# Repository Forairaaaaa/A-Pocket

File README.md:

# A-Pocket - 基于全志A133的掌上终端

视频介绍：[【开源】 自 制 手 机 ：【一】PDA？_哔哩哔哩_bilibili](https://www.bilibili.com/video/BV11t4y1W7DJ#reply114174036736)

虽然是奔着DIY手机去的，不知咋的就做成PDA了（

由于屏幕特殊，性价比极低，不建议复刻除核心板外的其他东西。

### 硬件组成

- **核心板**：板载全志A133邮票孔模块、USB-OTG、USB-Debug、带MIC的3.5mm耳机接口、扬声器接口、电池接口、MPU6050、RTC等，单板即可满足正常工作。另外由板对板引出显示屏接口和USB接口供拓展。未引出A133提供的摄像头接口。
- **拓展板**：板载LCD背光电路、USB5V的DC-DC升压电路和USB-HUB电路等。
- **散热**：背壳贴石墨烯，由导热硅垫传热

### 软件组成

核心模组厂商提供了安卓10和Ubuntu的镜像，要适配屏幕只需要简单修改设备树的配置文件即可。

### 物件参考链接

- [HelperBoard A133核心板（安卓10、ub，全志A133，内置5G-WIFI）-淘宝网 (taobao.com)](https://item.taobao.com/item.htm?spm=a1z09.2.0.0.fae32e8dKwhqRd&id=646476965103&_u=o2bdtj0f16a5)
- [适用智力快车儿童视频学习机早教机锂电池3.7V大容量10000mah充电-tmall.com天猫](https://detail.tmall.com/item.htm?id=613087896696&spm=a1z09.2.0.0.fae32e8dKwhqRd&_u=o2bdtj0fb0d2)   955565
- [3.8寸IPS液晶显示模块 电容触摸屏1024*600 JD9168, LVDS接口-tmall.com天猫](https://detail.tmall.com/item.htm?id=652122490131&spm=a1z09.2.0.0.fae32e8dKwhqRd&_u=o2bdtj0f7da0)

### 缺点

屏幕性价比低，屏占比低，核心模组也比较贵

板对板连接导致厚度大，扬声器音质很烂

### 待改进

改用量产的手机MIPI屏幕，但需要学写驱动（泪目

主控想改用RK3399或RK3588，但价格~~

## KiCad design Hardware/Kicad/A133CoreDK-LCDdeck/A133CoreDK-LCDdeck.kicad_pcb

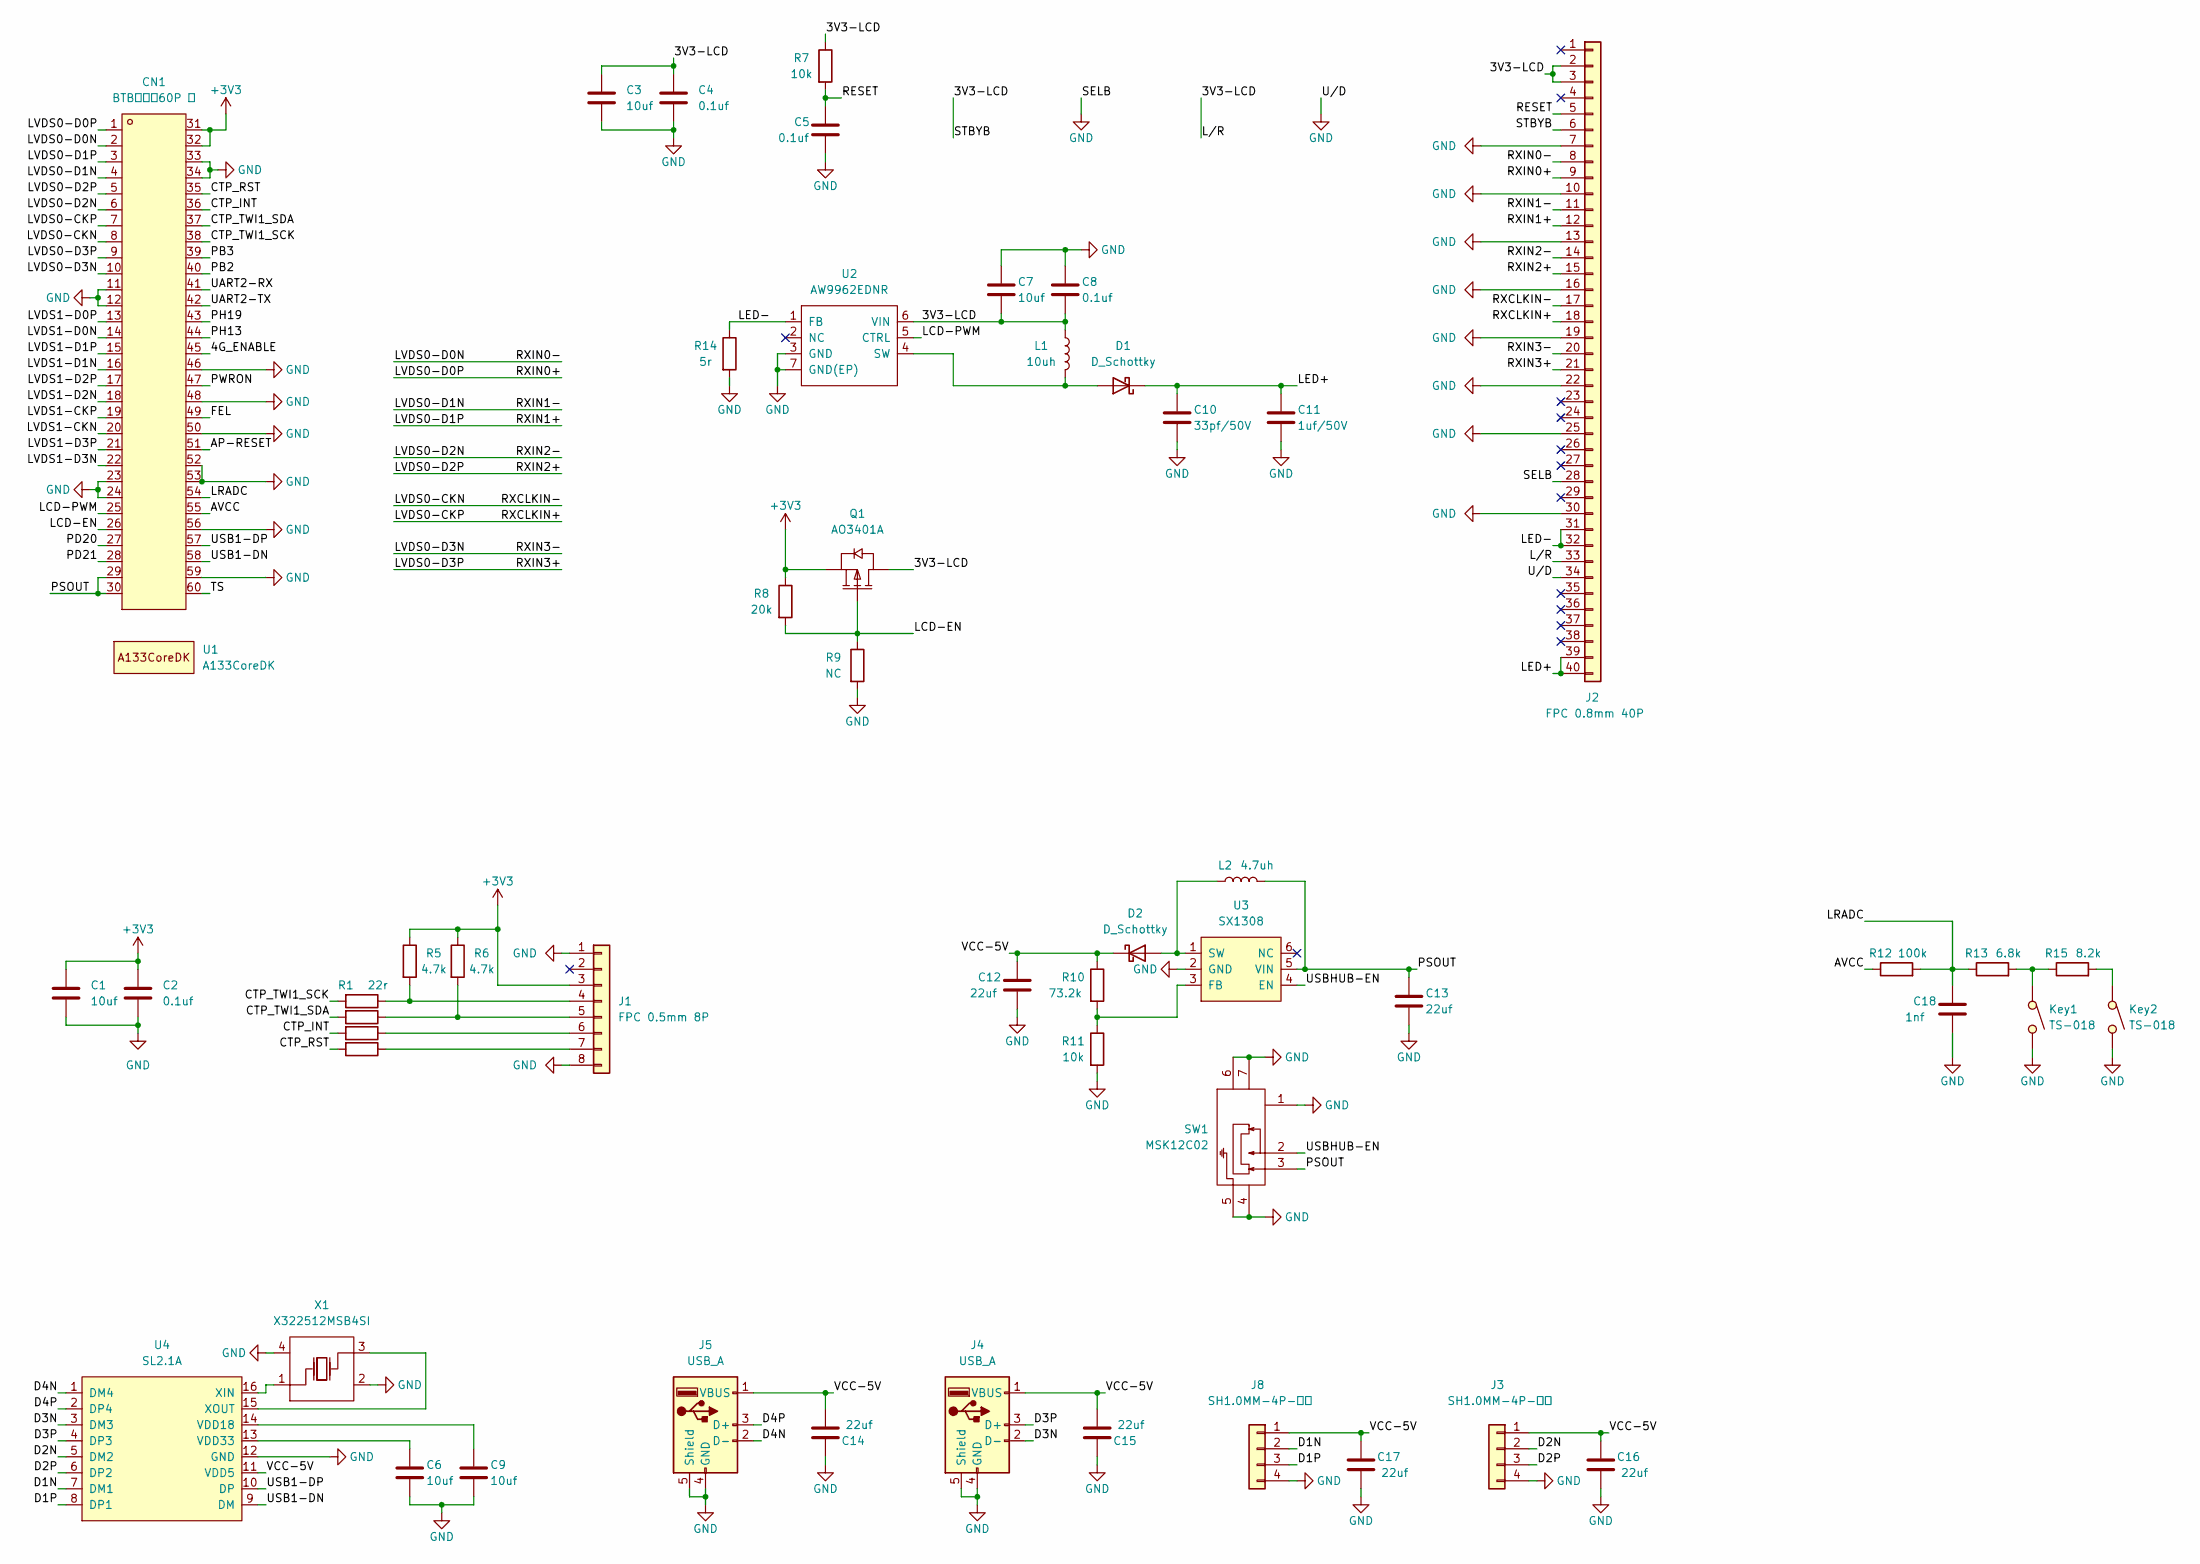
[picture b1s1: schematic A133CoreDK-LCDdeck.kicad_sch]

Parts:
C1, C3, C6, C7, C9: 10uf; C_0402_1005Metric
C2, C4, C5, C8: 0.1uf; C_0402_1005Metric
C10: 33pf/50V; C_0603_1608Metric
C11: 1uf/50V; C_0603_1608Metric
C12, C13, C14, C15, C16, C17: 22uf; C_0603_1608Metric
C18: 1nf; C_0402_1005Metric
CN1: BTB板对板60P 母
D1, D2: D_Schottky; D_SOD-123
J1: FPC 0.5mm 8P; TE_0-1734839-8_1x08-1MP_P0.5mm_Horizontal
J2: FPC 0.8mm 40P; TE_4-1734839-0_1x40-1MP_P0.5mm_Horizontal
J3, J8: SH1.0MM-4P-卧贴; SH1.0MM-卧贴-4P-CONN-SMD_1.0T-4P
J4, J5: USB_A; USB-A-SMD_FUS270-FSBW5K
Key1, Key2: TS-018; SW-SMD_TS24CA
L1: 10uh; CD32贴片电感-IND-SMD_L3.5-W3.0
L2: 4.7uh; CD32贴片电感-IND-SMD_L3.5-W3.0
Q1: AO3401A; SOT-23
R1, R2, R3, R4: 22r; R_0402_1005Metric
R5, R6: 4.7k; R_0402_1005Metric
R7, R11: 10k; R_0402_1005Metric
R8: 20k; R_0402_1005Metric
R9: NC; R_0402_1005Metric
R10: 73.2k; R_0402_1005Metric
R12: 100k; R_0402_1005Metric
R13: 6.8k; R_0402_1005Metric
R14: 5r; R_0402_1005Metric
R15: 8.2k; R_0402_1005Metric
SW1: MSK12C02; SW-TH_MSK12C02
U1: A133CoreDK
U2: AW9962EDNR; TDFN-6_L2.0-W2.0-P0.65-BL-EP
U3: SX1308; SOT-23-6
U4: SL2.1A; SOP-16_3.9x9.9mm_P1.27mm
X1: X322512MSB4SI; OSC-SMD_4P-L3.2-W2.5-BL

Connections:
+3V3: C1.1, C2.1, CN1.31, CN1.32, J1.3, Q1.2 (S), R5.1, R6.1, R8.1
/3V3-LCD: C3.1, C4.1, C7.2, C8.2, J2.2, J2.3, J2.6, J2.33, L1.1, Q1.3 (D), R7.1, U2.6 (VIN)
/4G_ENABLE: CN1.45
/AP-RESET: CN1.51
/AVCC: CN1.55, R12.1
/CTP_INT: CN1.36, R3.2
/CTP_RST: CN1.35, R4.2
/CTP_TWI1_SCK: CN1.38, R1.2
/CTP_TWI1_SDA: CN1.37, R2.2
/D1N: J8.2, U4.7 (DM1)
/D1P: J8.3, U4.8 (DP1)
/D2N: J3.2, U4.5 (DM2)
/D2P: J3.3, U4.6 (DP2)
/D3N: J4.2 (D-), U4.3 (DM3)
/D3P: J4.3 (D+), U4.4 (DP3)
/D4N: J5.2 (D-), U4.1 (DM4)
/D4P: J5.3 (D+), U4.2 (DP4)
/FEL: CN1.49
/LCD-EN: CN1.26, Q1.1 (G), R8.2, R9.1
/LCD-PWM: CN1.25, U2.5 (CTRL)
/LED+: C10.1, C11.1, D1.1 (K), J2.39, J2.40
/LED-: J2.31, J2.32, R14.1, U2.1 (FB)
/LRADC: C18.1, CN1.54, R12.2, R13.1
/LVDS0-CKN: CN1.8, J2.17
/LVDS0-CKP: CN1.7, J2.18
/LVDS0-D0N: CN1.2, J2.8
/LVDS0-D0P: CN1.1, J2.9
/LVDS0-D1N: CN1.4, J2.11
/LVDS0-D1P: CN1.3, J2.12
/LVDS0-D2N: CN1.6, J2.14
/LVDS0-D2P: CN1.5, J2.15
/LVDS0-D3N: CN1.10, J2.20
/LVDS0-D3P: CN1.9, J2.21
/LVDS1-CKN: CN1.20
/LVDS1-CKP: CN1.19
/LVDS1-D0N: CN1.14
/LVDS1-D0P: CN1.13
/LVDS1-D1N: CN1.16
/LVDS1-D1P: CN1.15
/LVDS1-D2N: CN1.18
/LVDS1-D2P: CN1.17
/LVDS1-D3N: CN1.22
/LVDS1-D3P: CN1.21
/PB2: CN1.40
/PB3: CN1.39
/PD20: CN1.27
/PD21: CN1.28
/PH13: CN1.44
/PH19: CN1.43
/PSOUT: C13.1, CN1.29, CN1.30, L2.2, SW1.3, U3.5 (VIN)
/PWRON: CN1.47
/RESET: C5.1, J2.5, R7.2
/TS: CN1.60
/UART2-RX: CN1.41
/UART2-TX: CN1.42
/USB1-DN: CN1.58, U4.9 (DM)
/USB1-DP: CN1.57, U4.10 (DP)
/USBHUB-EN: SW1.2, U3.4 (EN)
/VCC-5V: C12.1, C14.2, C15.2, C16.1, C17.1, D2.1 (K), J3.1, J4.1 (VBUS), J5.1 (VBUS), J8.1, R10.1, U4.11 (VDD5)
GND: C1.2, C2.2, C3.2, C4.2, C5.2, C6.2, C7.1, C8.1, C9.2, C10.2, C11.2, C12.2, C13.2, C14.1, C15.1, C16.2, C17.2, C18.2, CN1.11, CN1.12, CN1.23, CN1.24, CN1.33, CN1.34, CN1.46, CN1.48, CN1.50, CN1.52, CN1.53, CN1.56, CN1.59, J1.1, J1.8, J2.7, J2.10, J2.13, J2.16, J2.19, J2.22, J2.25, J2.28, J2.30, J2.34, J3.4, J4.4 (GND), J4.5 (Shield), J5.4 (GND), J5.5 (Shield), J8.4, Key1.2, Key2.2, R9.2, R11.2, R14.2, SW1.1, SW1.4, SW1.5, SW1.6, SW1.7, U2.3 (GND), U2.7 (GND(EP)), U3.2 (GND), U4.12 (GND), X1.2 (GND), X1.4 (GND)
unnamed: C6.1, U4.13 (VDD33)
unnamed: C9.1, U4.14 (VDD18)
unnamed: D1.2 (A), L1.2, U2.4 (SW)
unnamed: D2.2 (A), L2.1, U3.1 (SW)
unnamed: J1.4, R1.1, R5.2
unnamed: J1.5, R2.1, R6.2
unnamed: J1.6, R3.1
unnamed: J1.7, R4.1
unnamed: Key1.1, R13.2, R15.1
unnamed: Key2.1, R15.2
unnamed: R10.2, R11.1, U3.3 (FB)
unnamed: U4.15 (XOUT), X1.3 (OSC2)
unnamed: U4.16 (XIN), X1.1 (OSC1)

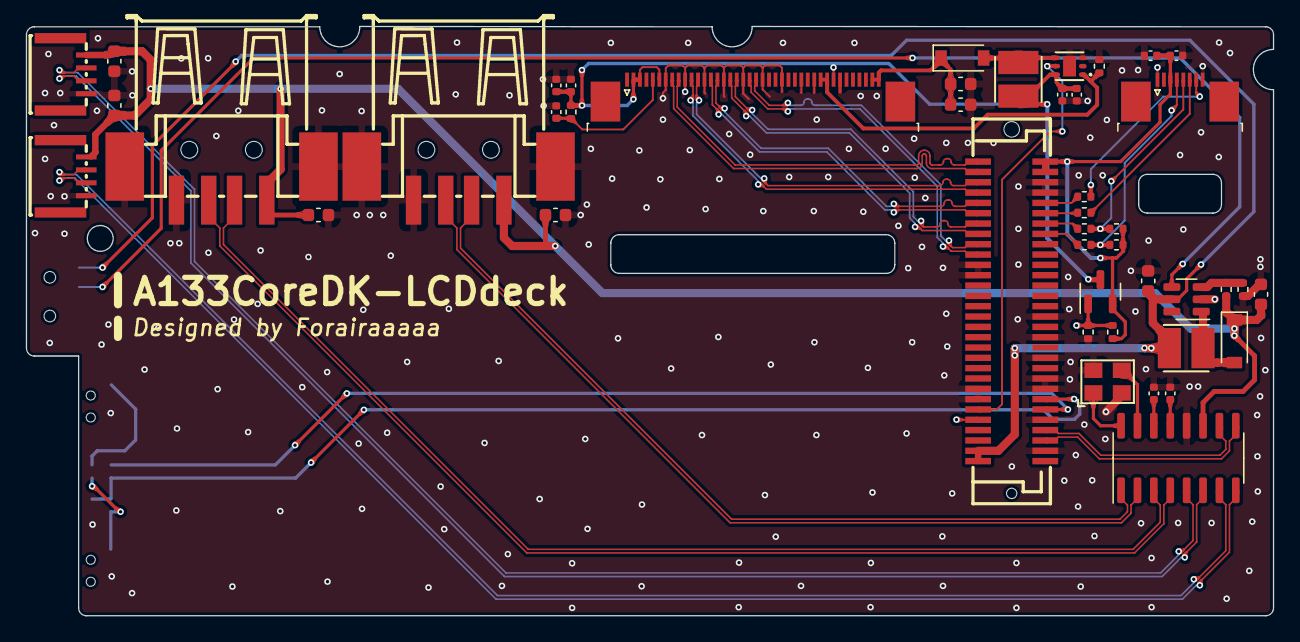
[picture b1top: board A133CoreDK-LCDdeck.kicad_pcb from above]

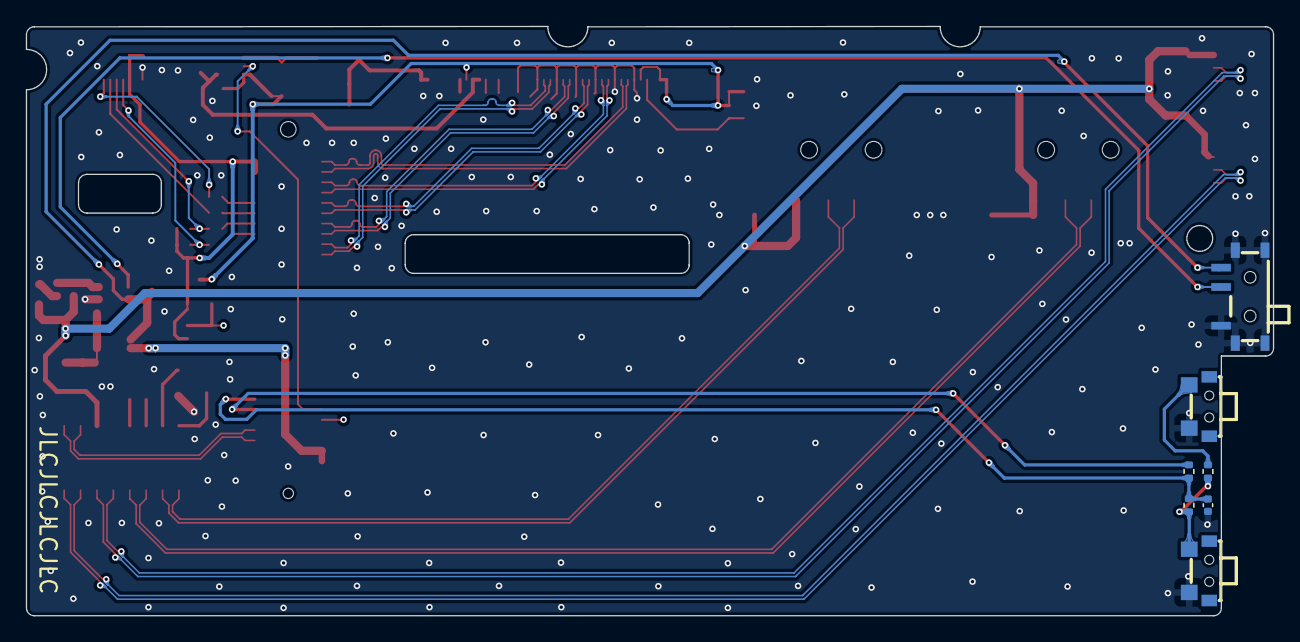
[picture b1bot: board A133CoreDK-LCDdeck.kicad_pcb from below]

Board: 4 copper layers, 96.6 x 45.6 mm, 53 parts (7 on the bottom side), 50 nets.

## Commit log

2022-05-24 add README.md
